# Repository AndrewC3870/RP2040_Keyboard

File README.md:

# RP2040_Keyboard
**Custom RP2040 mini keyboard for small portable projects!**

## Features
* **Microcontroller:** RP2040
* **Layout:** 5x13 Ortholinear
* **Special Features:** Integrated Left D-pad and Right Action buttons directly in the QMK matrix.
* **Firmware:** QMK
---
## Keymap Layout
The default keymap includes a standard typing base layer, an Fn layer with navigation and F-keys, and dedicated hardware gamepad keys mapped to the outer columns (this was made using simple buttons footprint for custom soldering, also can be replaced with functional buttons).

* **Gamepad Left:** `Up`, `Down`, `Left`, `Right`
* **Gamepad Right:** `Y`, `A`, `X`, `B`
* **Bumpers:** `Page Up` (L1), `Page Down` (R1)

Also the test pads I added can be used to solder analog devices such as joystick or analog trigger.
If decided to add this features, then you'll need to add this changes into code and configure the keyboard.

---
## Flashing Instructions
**The code is for my specific build, but it can be easily change to satisfy your requirements**

To compile and flash this firmware, you will need the [QMK CLI](https://docs.qmk.fm/#/newbs_getting_started) installed.

1. Clone the `qmk_firmware` repository.
2. Clone or download this repository and place the `rp2040_keyboard` folder from `setup` into `qmk_firmware/keyboards/`.
3. Put your keyboard into bootloader mode.
4. Run the following command from the root of your `qmk_firmware` directory:

```bash
qmk flash -kb rp2040_keyboard -km default

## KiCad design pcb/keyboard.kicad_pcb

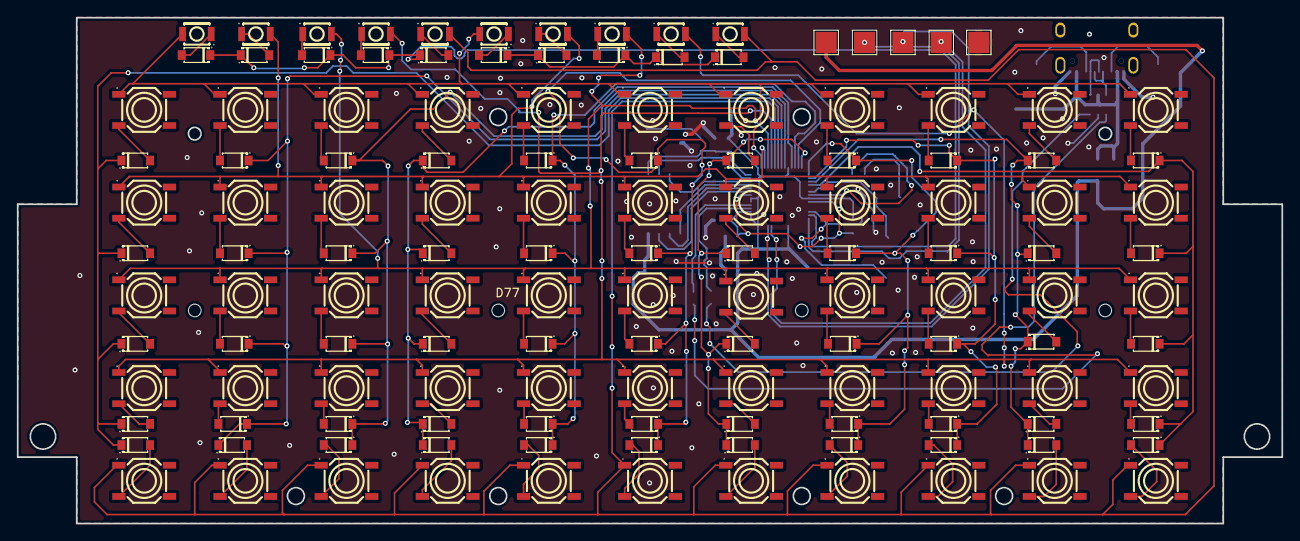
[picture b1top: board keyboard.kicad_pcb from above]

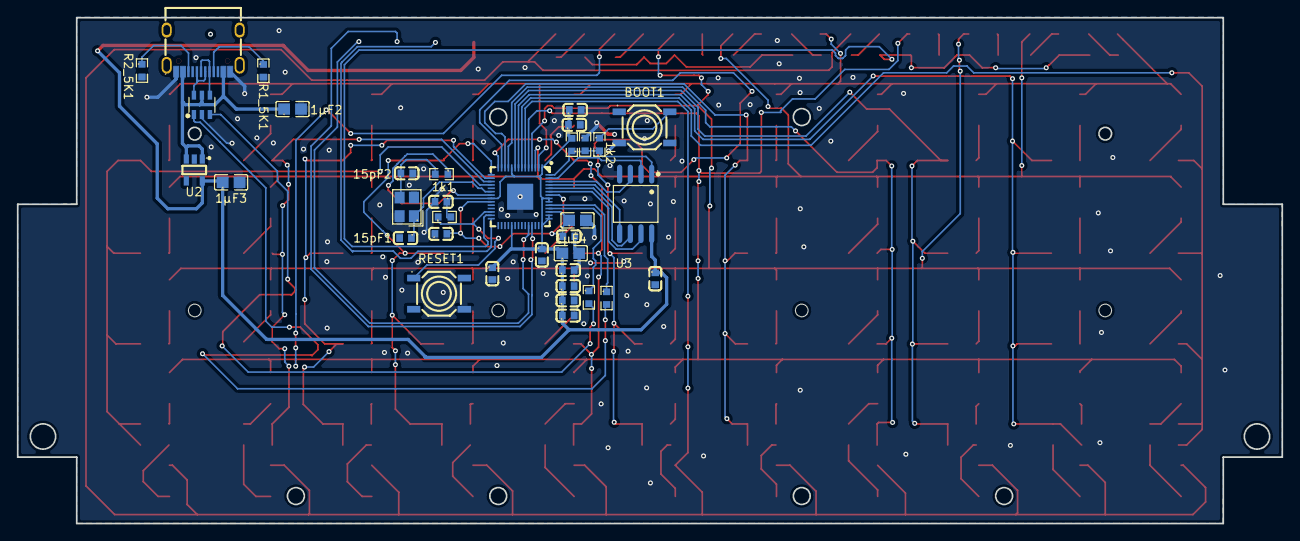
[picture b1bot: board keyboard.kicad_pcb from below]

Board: 2 copper layers, 150.0 x 60.0 mm, 170 parts (35 on the bottom side), 109 nets.

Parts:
1k1, 1k2: RC0603FR-071KL; R0603
1µF1, 1µF2, 1µF3, 1µF4: CC0805KKX5R6BB106; C0805
3V3: TestPoint; TestPoint_Pad_2.5x2.5mm
10k1, 10k2, 10k3: RC0603FR-0710KL; R0603
15pF1, 15pF2: CC0603JRNPO9BN150; C0603
27R1, 27R2: RC0603FR-0727RL; R0603
100nF1, 100nF2, 100nF3, 100nF4, 100nF5, 100nF6, 100nF7, 100nF8, 100nF9, 100nF10, 100nF11, 100nF12: CC0603KRX7R8BB104; C0603
BOOT1: K2-1187SQ-A1SW-06; SW-SMD_4P-L5.2-W5.2-P3.70-LS6.4
CLICK1: TestPoint; TestPoint_Pad_2.5x2.5mm
D1: USBLC6-2SC6; SOT-23-6_L2.9-W1.6-P0.95-LS2.8-BL
D66, D67, D68, D69, D70, D71, D72, D73, D74, D75, D76, D77, D78, D79, D80, D81, D82, D83, D84, D85, D86, D87, D88, D89, D90, D91, D92, D93, D94, D95, D96, D97, D98, D99, D100, D111, D112, D113, D114, D115, D116, D117, D118, D119, D120, D121, D122, D123, D124, D125, D126, D127, D128, D129, D130, D131, D132, D133, D134, D135, D136, D137, D138, D139, D140: 1N4148W-C84367; SOD-123_L2.8-W1.8-LS3.7-RD
GND1: TestPoint; TestPoint_Pad_2.5x2.5mm
R1_5K1, R2_5K1: RC0603FR-075K1L; R0603
RESET1: K2-1187SQ-A1SW-06; SW-SMD_4P-L5.2-W5.2-P3.70-LS6.4
SW1, SW2, SW3, SW4, SW5, SW6, SW7, SW8, SW9, SW10, SW11, SW12, SW13, SW14, SW15, SW16, SW17, SW18, SW19, SW20, SW21, SW22, SW23, SW24, SW25, SW26, SW27, SW28, SW29, SW30, SW31, SW32, SW33, SW34, SW35, SW36, SW37, SW38, SW39, SW40, SW41, SW42, SW43, SW44, SW45, SW46, SW47, SW48, SW49, SW50, SW51, SW52, SW53, SW54, SW55: K2-1187SQ-A1SW-06; SW-SMD_4P-L5.2-W5.2-P3.70-LS6.4
SW56, SW57, SW58, SW59, SW60, SW61, SW62, SW63, SW64, SW65: B3U-1000P; KEY-SMD_B3U-1000PM
U1: RP2040; LQFN-56_L7.0-W7.0-P0.4-EP
U2: AP2112K-3.3TRG1; SOT-25-5_L2.9-W1.6-P0.95-LS2.8-BL
U3: W25Q16JVSSIQ; SOIC-8_L5.3-W5.3-P1.27-LS8.0-BL
USBC1: TYPE-C-31-M-12; USB-C_SMD-TYPE-C-31-M-12_1
X1: X322512MOB4SI; CRYSTAL-SMD_4P-L3.2-W2.5-BL
X2: TestPoint; TestPoint_Pad_2.5x2.5mm
Y1: TestPoint; TestPoint_Pad_2.5x2.5mm

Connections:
3V3: 1µF3.1, 1µF4.1, 3V3.1 (1_1), 10k1.2, 10k2.2, 100nF1.1, 100nF2.1, 100nF3.1, 100nF4.1, 100nF5.1, 100nF6.1, 100nF7.1, 100nF8.1, 100nF9.1, 100nF10.1, U1.1 (IOVDD), U1.10 (IOVDD), U1.22 (IOVDD), U1.33 (IOVDD), U1.42 (IOVDD), U1.43 (ADC_AVDD), U1.44 (VREG_IN), U1.48 (USB_VDD), U1.49 (IOVDD), U2.5 (VOUT), U3.8 (VCC)
5V_USB: 1µF2.1, D1.5, U2.1 (VIN), U2.3 (EN), USBC1.A4B9 (VBUS), USBC1.B4A9 (VBUS)
CLICK: CLICK1.1 (1_1), U1.28 (GPIO17)
CLK: U1.52 (QSPI_SCLK), U3.6 (CLK)
COL_1: D66.1 (C), D67.1 (C), D68.1 (C), D69.1 (C), D70.1 (C), U1.7 (GPIO5)
COL_2: D71.1 (C), D72.1 (C), D73.1 (C), D74.1 (C), D75.1 (C), U1.8 (GPIO6)
COL_3: D76.1 (C), D77.1 (C), D78.1 (C), D79.1 (C), D80.1 (C), U1.9 (GPIO7)
COL_4: D81.1 (C), D82.1 (C), D83.1 (C), D84.1 (C), D85.1 (C), U1.11 (GPIO8)
COL_5: D86.1 (C), D87.1 (C), D88.1 (C), D89.1 (C), D90.1 (C), U1.12 (GPIO9)
COL_6: D91.1 (C), D92.1 (C), D93.1 (C), D94.1 (C), D95.1 (C), U1.13 (GPIO10)
COL_7: D96.1 (C), D97.1 (C), D98.1 (C), D99.1 (C), D100.1 (C), U1.14 (GPIO11)
COL_8: D132.1 (C), D133.1 (C), D135.1 (C), D137.1 (C), D139.1 (C), U1.15 (GPIO12)
COL_9: D131.1 (C), D134.1 (C), D136.1 (C), D138.1 (C), D140.1 (C), U1.16 (GPIO13)
COL_10: D111.1 (C), D112.1 (C), D113.1 (C), D114.1 (C), D115.1 (C), U1.17 (GPIO14)
COL_11: D116.1 (C), D117.1 (C), D118.1 (C), D119.1 (C), D120.1 (C), U1.18 (GPIO15)
COL_12: D126.1 (C), D127.1 (C), D128.1 (C), D129.1 (C), D130.1 (C), U1.27 (GPIO16)
COL_13: D121.1 (C), D122.1 (C), D123.1 (C), D124.1 (C), D125.1 (C)
CS: 1k2.2, 10k2.1, 10k3.2, U1.56 (QSPI_SS), U3.1 (/CS)
D+: D1.6, USBC1.A6 (DP1), USBC1.B6 (DP2)
D-: D1.4, USBC1.A7 (DN1), USBC1.B7 (DN2)
DI: U1.53 (QSPI_SD0), U3.5 (DI/IO0)
DO: U1.55 (QSPI_SD1), U3.2 (DO/IO1)
GND: 1µF1.2, 1µF2.2, 1µF3.2, 1µF4.2, 10k3.1, 15pF1.2, 15pF2.2, 100nF1.2, 100nF2.2, 100nF3.2, 100nF4.2, 100nF5.2, 100nF6.2, 100nF7.2, 100nF8.2, 100nF9.2, 100nF10.2, 100nF11.1, 100nF12.1, BOOT1.3, D1.2, GND1.1 (1_1), R1_5K1.2, R2_5K1.2, RESET1.4, U1.57 (GND), U2.2 (GND), U3.4 (GND), USBC1.A1B12 (GND), USBC1.B1A12 (GND), X1.2 (GND), X1.4 (GND)
HOLD: U1.51 (QSPI_SD3), U3.7 (IO3)
unnamed: 1k2.1, BOOT1.2
unnamed: 27R1.2, D1.1
unnamed: 27R2.2, D1.3
unnamed: D66.2 (A), SW1.3
unnamed: D67.2 (A), SW2.3
unnamed: D68.2 (A), SW3.3
unnamed: D69.2 (A), SW4.3
unnamed: D70.2 (A), SW5.3
unnamed: D71.2 (A), SW6.3
unnamed: D72.2 (A), SW7.3
unnamed: D73.2 (A), SW8.3
unnamed: D74.2 (A), SW9.3
unnamed: D75.2 (A), SW10.3
unnamed: D76.2 (A), SW11.3
unnamed: D77.2 (A), SW12.3
unnamed: D78.2 (A), SW13.3
unnamed: D79.2 (A), SW14.3
unnamed: D80.2 (A), SW15.3
unnamed: D81.2 (A), SW16.3
unnamed: D82.2 (A), SW17.3
unnamed: D83.2 (A), SW18.3
unnamed: D84.2 (A), SW19.3
unnamed: D85.2 (A), SW20.3
unnamed: D86.2 (A), SW21.3
unnamed: D87.2 (A), SW22.3
unnamed: D88.2 (A), SW23.3
unnamed: D89.2 (A), SW24.3
unnamed: D90.2 (A), SW25.3
unnamed: D91.2 (A), SW26.3
unnamed: D92.2 (A), SW27.3
unnamed: D93.2 (A), SW28.3
unnamed: D94.2 (A), SW29.3
unnamed: D95.2 (A), SW30.3
unnamed: D96.2 (A), SW31.3
unnamed: D97.2 (A), SW32.3
unnamed: D98.2 (A), SW33.3
unnamed: D99.2 (A), SW34.3
unnamed: D100.2 (A), SW35.3
unnamed: D111.2 (A), SW46.3
unnamed: D112.2 (A), SW47.3
unnamed: D113.2 (A), SW48.3
unnamed: D114.2 (A), SW49.3
unnamed: D115.2 (A), SW50.3
unnamed: D116.2 (A), SW51.3
unnamed: D117.2 (A), SW52.3
unnamed: D118.2 (A), SW53.3
unnamed: D119.2 (A), SW54.3
unnamed: D120.2 (A), SW55.3
unnamed: D121.2 (A), SW61.1
unnamed: D122.2 (A), SW62.1
unnamed: D123.2 (A), SW63.1
unnamed: D124.2 (A), SW64.1
unnamed: D125.2 (A), SW65.1
unnamed: D126.2 (A), SW56.1
unnamed: D127.2 (A), SW57.1
unnamed: D128.2 (A), SW58.1
unnamed: D129.2 (A), SW59.1
unnamed: D130.2 (A), SW60.1
unnamed: D131.2 (A), SW41.3
unnamed: D132.2 (A), SW36.3
unnamed: D133.2 (A), SW37.3
unnamed: D134.2 (A), SW42.3
unnamed: D135.2 (A), SW38.3
unnamed: D136.2 (A), SW43.3
unnamed: D137.2 (A), SW39.3
unnamed: D138.2 (A), SW44.3
unnamed: D139.2 (A), SW40.3
unnamed: D140.2 (A), SW45.3
unnamed: 27R2.1, U1.46 (USB_DM)
unnamed: 27R1.1, U1.47 (USB_DP)
unnamed: 1µF1.1, 100nF11.2, 100nF12.2, U1.23 (DVDD), U1.45 (VREG_VOUT), U1.50 (DVDD)
unnamed: R1_5K1.1, USBC1.A5 (CC1)
unnamed: R2_5K1.1, USBC1.B5 (CC2)
unnamed: 1k1.2, 15pF2.1, X1.3 (OSC2)
ROW_1: SW1.1, SW6.1, SW11.1, SW16.1, SW21.1, SW26.1, SW31.1, SW36.1, SW41.1, SW46.1, SW51.1, SW56.2, SW61.2, U1.2 (GPIO0)
ROW_2: SW2.1, SW7.1, SW12.1, SW17.1, SW22.1, SW27.1, SW32.1, SW37.1, SW42.1, SW47.1, SW52.1, SW57.2, SW62.2, U1.3 (GPIO1)
ROW_3: SW3.1, SW8.1, SW13.1, SW18.1, SW23.1, SW28.1, SW33.1, SW38.1, SW43.1, SW48.1, SW53.1, SW58.2, SW63.2, U1.4 (GPIO2)
ROW_4: SW4.1, SW9.1, SW14.1, SW19.1, SW24.1, SW29.1, SW34.1, SW39.1, SW44.1, SW49.1, SW54.1, SW59.2, SW64.2, U1.5 (GPIO3)
ROW_5: SW5.1, SW10.1, SW15.1, SW20.1, SW25.1, SW30.1, SW35.1, SW40.1, SW45.1, SW50.1, SW55.1, SW60.2, SW65.2, U1.6 (GPIO4)
RUN: 10k1.1, RESET1.1, U1.26 (RUN)
WP: U1.54 (QSPI_SD2), U3.3 (IO2)
X-AX: U1.38 (GPIO26_ADC0), X2.1 (1_1)
XIN: 15pF1.1, U1.20 (XIN), X1.1 (OSC1)
XOUT: 1k1.1, U1.21 (XOUT)
Y-AX: U1.39 (GPIO27_ADC1), Y1.1 (1_1)

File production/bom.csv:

Designator,Footprint,Quantity,Value,LCSC Part #
"100NF1, 100NF10, 100NF11, 100NF12, 100NF2, 100NF3, 100NF4, 100NF5, 100NF6, 100NF7, 100NF8, 100NF9",C0603,12,CC0603KRX7R8BB104,C92490
"10K1, 10K2, 10K3",R0603,3,RC0603FR-0710KL,C98220
"15PF1, 15PF2",C0603,2,CC0603JRNPO9BN150,C107037
"1K1, 1K2",R0603,2,RC0603FR-071KL,C22548
"1ΜF1, 1ΜF2, 1ΜF3, 1ΜF4",C0805,4,CC0805KKX5R6BB106,C89832
"27R1, 27R2",R0603,2,RC0603FR-0727RL,C137753
"3V3, CLICK1, GND1, X2, Y1",TestPoint_Pad_2.5x2.5mm,5,TestPoint,
"BOOT1, RESET1, SW1, SW10, SW11, SW12, SW13, SW14, SW15, SW16, SW17, SW18, SW19, SW2, SW20, SW21, SW22, SW23, SW24, SW25, SW26, SW27, SW28, SW29, SW3, SW30, SW31, SW32, SW33, SW34, SW35, SW36, SW37, SW38, SW39, SW4, SW40, SW41, SW42, SW43, SW44, SW45, SW46, SW47, SW48, SW49, SW5, SW50, SW51, SW52, SW53, SW54, SW55, SW6, SW7, SW8, SW9",SW-SMD_4P-L5.2-W5.2-P3.70-LS6.4,57,K2-1187SQ-A1SW-06,C707331
D1,SOT-23-6_L2.9-W1.6-P0.95-LS2.8-BL,1,USBLC6-2SC6,C7519
"D100, D111, D112, D113, D114, D115, D116, D117, D118, D119, D120, D121, D122, D123, D124, D125, D126, D127, D128, D129, D130, D131, D132, D133, D134, D135, D136, D137, D138, D139, D140, D66, D67, D68, D69, D70, D71, D72, D73, D74, D75, D76, D77, D78, D79, D80, D81, D82, D83, D84, D85, D86, D87, D88, D89, D90, D91, D92, D93, D94, D95, D96, D97, D98, D99",SOD-123_L2.8-W1.8-LS3.7-RD,65,1N4148W-C84367,C84367
"R1_5K1, R2_5K1",R0603,2,RC0603FR-075K1L,C105580
"SW56, SW57, SW58, SW59, SW60, SW61, SW62, SW63, SW64, SW65",KEY-SMD_B3U-1000PM,10,B3U-1000P,C231329
U1,LQFN-56_L7.0-W7.0-P0.4-EP,1,RP2040,C2040
U2,SOT-25-5_L2.9-W1.6-P0.95-LS2.8-BL,1,AP2112K-3.3TRG1,C51118
U3,SOIC-8_L5.3-W5.3-P1.27-LS8.0-BL,1,W25Q16JVSSIQ,C82317
USBC1,USB-C_SMD-TYPE-C-31-M-12_1,1,TYPE-C-31-M-12,C165948
X1,CRYSTAL-SMD_4P-L3.2-W2.5-BL,1,X322512MOB4SI,C70565
